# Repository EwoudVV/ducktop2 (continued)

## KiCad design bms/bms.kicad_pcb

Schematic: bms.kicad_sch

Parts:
C724: 470n 25V CP1; effective >=100n at11V; C_0603_1608Metric; MPN GRM188R71E474KA12D
C840: 1u 25V BAT supply; C_0603_1608Metric; MPN GRM188R71E105KA12D
C841: 1u 10V REG18; C_0603_1608Metric; MPN GRM188R71A105KA61D
C845: 4.7u 10V REG1; effective >=1u; C_0805_2012Metric; MPN GRM21BR71A475KA73L
C846: 100n 50V differential current filter; C_0603_1608Metric; MPN GRM188R71H104KA93D
C852, C853, C854, C855: 220n 50V cell filter; C_0603_1608Metric; MPN GRM188R71H224KA93D
C880: 1u 50V REGIN input; C_0805_2012Metric; MPN GRM21BR71H105KA12L
C881: 10u 25V REGIN; effective >=2u; C_0805_2012Metric; MPN GRM21BZ71E106KE15L
C882: 100n 25V C0G startup ramp; C_1206_3216Metric; MPN C1206C104F3GECAUTO
C883: 1u 50V startup input; C_0805_2012Metric; MPN GRM21BR71H105KA12L
C884: 220n 50V startup output; effective >=100n; C_0603_1608Metric; MPN GRM188R71H224KA93D
C2200: 100n 50V thermal regulator input; C_0603_1608Metric; MPN GRM188R71H104KA93D
C2201: 10u 50V thermal bias; require Ceff >=2u; C_1206_3216Metric; MPN CGA5L1X7R1H106K160AC
C2211, C2212, C2213: 10n 50V NTC sense filter; C_0603_1608Metric; MPN GRM188R71H103KA01D
C2221, C2222, C2223: 100n 50V comparator supply; C_0603_1608Metric; MPN GRM188R71H104KA93D
C2230: 100n 50V thermal supervisor supply; C_0603_1608Metric; MPN GRM188R71H104KA93D
C2231: 100n 50V thermal buffer supply; C_0603_1608Metric; MPN GRM188R71H104KA93D
C2232: 100n 50V OFF-bias bypass; C_0603_1608Metric; MPN GRM188R71H104KA93D
C2240, C2241, C2242: 10n 50V thermal reference filter; C_0603_1608Metric; MPN GRM188R71H103KA01D
C2243: 10n 50V thermal reference filter; C_0402_1005Metric; MPN C1005X7R1H103K050BB
C2250, C2251: 100n 50V I2C isolator supply; C_0603_1608Metric; MPN GRM188R71H104KA93D
C2252: 100n 50V bus buffer supply; C_0603_1608Metric; MPN GRM188R71H104KA93D
C2253: 100n 50V readiness buffer supply; C_0603_1608Metric; MPN GRM188R71H104KA93D
C2255, C2256: 100n 50V readiness isolator supply; C_0603_1608Metric; MPN GRM188R71H104KA93D
C2257: 1u 10V control input; C_0603_1608Metric; MPN GRM188R71A105KA61D
C2258: 1u 10V control output; C_0603_1608Metric; MPN GRM188R71A105KA61D
C2270, C2271: 10n 50V C0G differential filter; C_0603_1608Metric; MPN GRM1885C1H103JA01J
C2272: 1u 10V reference input; C_0603_1608Metric; MPN GRM188R71A105KA61D
C2273: 1u 10V reference output; C_0603_1608Metric; MPN GRM188R71A105KA61D
C2274, C2275: 100n 50V current guard supply; C_0603_1608Metric; MPN GRM188R71H104KA93D
C2276, C2277: 10n 50V current reference filter; C_0603_1608Metric; MPN GRM188R71H103KA01D
C2278: 100n 50V current supervisor supply; C_0603_1608Metric; MPN GRM188R71H104KA93D
C2279: 100n 50V readiness logic supply; C_0603_1608Metric; MPN GRM188R71H104KA93D
C2280: 100n 50V reference output; C_0603_1608Metric; MPN GRM188R71H104KA93D
C2281: 1u 50V thermal switch input; C_0805_2012Metric; MPN GRM21BR71H105KA12L
D840: BAT54WS BAT supply reverse block; D_SOD-323; MPN BAT54WS-7-F
D847, D848: BZT52C15 gate-source clamp; D_SOD-123; MPN BZT52C15-7-F
D849: BZT52C5V1 startup permit VGS clamp; D_SOD-123; MPN BZT52C5V1-7-F
D2220, D2221: BAT54WS OFF-bias supply OR; D_SOD-323; MPN BAT54WS-7-F
F1: 10A fast pack fuse; Schurter_HCF_8.05x5mm; MPN 3-101-051
J2: raw pack power: 1 negative, 2 positive; WAGO_2060_452_SMD; MPN 2060-452/998-404
J2072: protected pack power; WAGO_2060_452_SMD; MPN 2060-452/998-404
J2074: isolated bms control; JST_SH_SM05B-SRSS-TB_1x05-1MP_P1.00mm_Horizontal; MPN SM05B-SRSS-TB(LF)(SN)
J2200: three cell probes: paired 1/2, 3/4, 5/6; JST_SH_SM06B-SRSS-TB_1x06-1MP_P1.00mm_Horizontal; MPN SM06B-SRSS-TB(LF)(SN)
J2201: cell taps: 1 cell 1, 2 cell 2; JST_GH_SM02B-GHS-TB_1x02-1MP_P1.25mm_Horizontal; MPN SM02B-GHS-TB(LF)(SN)
Q11: CSD18540Q5B high-side charge; CSD18540Q5B_DNK; MPN CSD18540Q5B
Q12: CSD18540Q5B high-side discharge; CSD18540Q5B_DNK; MPN CSD18540Q5B
Q2200: BSS138 CHG thermal CTR pull-down; SOT-23; MPN BSS138LT1G
Q2201: BSS138 DSG thermal CTR pull-down; SOT-23; MPN BSS138LT1G
Q2211: ZXMP6A13FTA PDSG signal translator; SOT-23; MPN ZXMP6A13FTA
Q2212: BSS138 independent discharge inhibit; SOT-23; MPN BSS138LT1G
R840: 100R BAT input filter; R_0603_1608Metric; MPN RC0603FR-07100RL
R841, R842, R843, R844: 75R 1% cell input/balance filter; R_0603_1608Metric; MPN RC0603FR-0775RL
R845: 100R SRP filter; R_0603_1608Metric; MPN RC0603FR-07100RL
R846: 100R SRN filter; R_0603_1608Metric; MPN RC0603FR-07100RL
R847, R848: 100R gate series; R_0603_1608Metric; MPN RC0603FR-07100RL
R849, R850: 1M gate-source; R_0603_1608Metric; MPN RC0603FR-071ML
R851: 10k PACK sense; R_0603_1608Metric; MPN RC0603FR-0710KL
R852: 10k LD sense; R_0603_1608Metric; MPN RC0603FR-0710KL
R870, R871: DNP 0R drive release; R_0603_1608Metric; MPN RC0603JR-070RL; not fitted
R872: DNP 0R startup drive release; R_0603_1608Metric; MPN RC0603JR-070RL; not fitted
R880, R881: 430R 1% 1.5W REGIN supply limiter; R_2512_6332Metric; MPN CRCW2512430RFKEGHP
R882: 100k reset default-low; R_0603_1608Metric; MPN RC0603FR-07100KL
R883: 10k TS1 termination; R_0603_1608Metric; MPN RC0603FR-0710KL
R884: 100k UVLO top; R_0603_1608Metric; MPN RC0603FR-07100KL
R885: 24.9k UVLO bottom; R_0603_1608Metric; MPN RC0603FR-0724K9L
R886: 402k latched current-limit mode; R_0603_1608Metric; MPN RC0603FR-07402KL
R887: 12k 0.1% 25ppm ILIM; R_0603_1608Metric; MPN TNPW060312K0BEEN
R888: 24k 0.1% 25ppm ILIM; R_0603_1608Metric; MPN TNPW060324K0BEEN
R889: 100k startup fault pull-up; R_0603_1608Metric; MPN RC0603FR-07100KL
R890: 1k PDSG translator gate; R_0603_1608Metric; MPN RC0603FR-071KL
R891: 1M translator gate-source; R_0603_1608Metric; MPN RC0603FR-071ML
R892: 100k startup shutdown top; R_0603_1608Metric; MPN RC0603FR-07100KL
R893: 33.2k startup shutdown default-low; R_0603_1608Metric; MPN RC0603FR-0733K2L
R894: 100k startup permit gate series; R_0603_1608Metric; MPN RC0603FR-07100KL
R2200: 1k 1% 0.75W raw thermal supply limiter; R_2010_5025Metric; MPN RC2010FK-071KL
R2201: 9.53k 0.1% 25ppm thermal bias fault bleed; R_0603_1608Metric; MPN RT0603BRD079K53L
R2210, R2213, R2216: 100k 0.1% 25ppm cell NTC pull-up; R_0603_1608Metric; MPN RT0603BRD07100KL
R2211, R2214: 10k 0.1% 25ppm NTC sense-lead limit; R_0603_1608Metric; MPN RT0603BRD0710KL
R2212, R2215, R2218: 10k 0.1% 25ppm NTC return-lead limit; R_0603_1608Metric; MPN RT0603BRD0710KL
R2217: 10k 0.1% 25ppm NTC sense-lead limit; R_0402_1005Metric; MPN RT0402BRD0710KL
R2230: 100k thermal charge-health pull-up; R_0603_1608Metric; MPN RC0603FR-07100KL
R2231: 100k thermal discharge-health pull-up; R_0603_1608Metric; MPN RC0603FR-07100KL
R2232: 47k thermal-ready pull-up; R_0603_1608Metric; MPN RC0603FR-0747KL
R2233: 1M thermal-ready default-low; R_0603_1608Metric; MPN RC0603FR-071ML
R2234, R2237: 1k thermal CTR gate series; R_0603_1608Metric; MPN RC0603FR-071KL
R2235, R2238: 100k thermal CTR gate default-off; R_0603_1608Metric; MPN RC0603FR-07100KL
R2236, R2239: 10k hardware OFF default-high; R_0603_1608Metric; MPN RC0603FR-0710KL
R2240: 243k 0.1% 25ppm CHG_COLD top; R_0603_1608Metric; MPN RT0603BRD07243KL
R2241, R2243, R2245, R2247: 499k 0.1% 25ppm thermal reference bottom; R_0603_1608Metric; MPN RT0603BRD07499KL
R2242: 634k 0.1% 25ppm CHG_HOT top; R_0603_1608Metric; MPN RT0603BRD07634KL
R2244: 147k 0.1% 25ppm DSG_COLD top; R_0603_1608Metric; MPN RT0603BRD07147KL
R2246: 845k 0.1% 25ppm DSG_HOT top; R_0603_1608Metric; MPN RT0603BRD07845KL
R2251: 100k raw health default-low; R_0603_1608Metric; MPN RC0603FR-07100KL
R2255: 100k control health default-low; R_0603_1608Metric; MPN RC0603FR-07100KL
R2258: 4.7k readiness output current limit; R_0603_1608Metric; MPN RC0603FR-074K7L
R2260, R2261: 4.7k 1% I2C pull-up; R_0603_1608Metric; MPN RC0603FR-074K7L
R2262, R2263, R2266, R2267: 2.2k 1% I2C pull-up; R_0603_1608Metric; MPN RC0603FR-072K2L
R2270: 10.2k 0.1% 25ppm current limit; R_0603_1608Metric; MPN TNPW060310K2BEEA
R2271: 26.7k 0.1% 25ppm current limit; R_0603_1608Metric; MPN TNPW060326K7BEEA
R2272: 16.9k 0.1% 25ppm current limit; R_0603_1608Metric; MPN TNPW060316K9BEEA
R2273: 31.6k 0.1% 25ppm current limit; R_0603_1608Metric; MPN TNPW060331K6BEEA
R2274: 10k current-ready pull-up; R_0603_1608Metric; MPN RC0603FR-0710KL
R2275: 100k current-ready default-low; R_0603_1608Metric; MPN RC0603FR-07100KL
R2276: 100k current reset pull-up; R_0603_1608Metric; MPN RC0603FR-07100KL
R2277: 100k 180..420ms current hold; R_0603_1608Metric; MPN RC0603FR-07100KL
R2278: 100k permission default-low; R_0603_1608Metric; MPN RC0603FR-07100KL
R2280, R2281, R2282, R2283: 4.99R 0.1% 25ppm sense filter; R_0603_1608Metric; MPN TNPW06034R99BEEA
R2290: 390k thermal switch default-off; R_0603_1608Metric; MPN RC0603FR-07390KL
RS11: 2mOhm 1% 6W four-terminal pack shunt; Bourns_CSS4J_4026_Kelvin; MPN CSS4J-4026K-2L00F
TH2201: 104JT-025 cell 1 insulated probe; MPN 104JT-025
TH2202: 104JT-025 cell 2 insulated probe; MPN 104JT-025
TH2203: 104JT-025 cell 3 insulated probe; MPN 104JT-025
TPB1: PACK_POS_RAW; TestPoint_Pad_D1.0mm
TPB2: BAT_PROT_VIN; TestPoint_Pad_D1.0mm
TPB3: PACK_POS_FUSED; TestPoint_Pad_D1.0mm
TPB4: BAT_PROT_FET_COMMON; TestPoint_Pad_D1.0mm
TPB5: PACK_NEG_RAW; TestPoint_Pad_D1.0mm
TPB6: FG_VSS; TestPoint_Pad_D1.0mm
TPB7: BQ_BAT; TestPoint_Pad_D1.0mm
TPB8: BQ_WAKE; TestPoint_Pad_D1.0mm
TPB9: BQ_RST_SHUT; TestPoint_Pad_D1.0mm
TPB10: BQ_REG1; TestPoint_Pad_D1.0mm
TPB11: BMS_SRP; TestPoint_Pad_D1.0mm
TPB12: BMS_SRN; TestPoint_Pad_D1.0mm
TPB13: BMS_RAW_SCL; TestPoint_Pad_D1.0mm
TPB14: BMS_RAW_SDA; TestPoint_Pad_D1.0mm
TPB15: BQ_ALERT_AWAKE; TestPoint_Pad_D1.0mm
TPB16: BQ_REGIN; TestPoint_Pad_D1.0mm
TPB20: THERM_3V3; TestPoint_Pad_D1.0mm
TPB21: THERM_READY; TestPoint_Pad_D1.0mm
TPB22: THERM_SENSE_1; TestPoint_Pad_D1.0mm
TPB23: THERM_SENSE_2; TestPoint_Pad_D1.0mm
TPB24: THERM_SENSE_3; TestPoint_Pad_D1.0mm
TPB25: BMS_CFETOFF; TestPoint_Pad_D1.0mm
TPB26: BMS_DFETOFF; TestPoint_Pad_D1.0mm
TPB27: BMS_PERMIT_READY; TestPoint_Pad_D1.0mm
TPB30: PDSG_FLT_N; TestPoint_Pad_D1.0mm
TPB31: PDSG_SHDN; TestPoint_Pad_D1.0mm
TPB32: PDSG_RTN; TestPoint_Pad_D1.0mm
TPB33: CURRENT_READY; TestPoint_Pad_D1.0mm
TPB34: CURRENT_CLR_N; TestPoint_Pad_D1.0mm
TPB35: BMS_CURRENT_REF; TestPoint_Pad_D1.0mm
U708: TPS70950DBVR REGIN supply; SOT-23-5; MPN TPS70950DBVR
U719: BQ76922RSNR three-cell monitor and protector; TI_RSN0032B_WQFN32_4x4mm; MPN BQ76922RSNR
U2200: TPS70933DBVR raw-pack thermal bias; SOT-23-5; MPN TPS70933DBVR
U2201: TLV1864PWR cell 1 thermal windows; TSSOP-14_4.4x5mm_P0.65mm; MPN TLV1864PWR
U2202: TLV1864PWR cell 2 thermal windows; TSSOP-14_4.4x5mm_P0.65mm; MPN TLV1864PWR
U2203: TLV1864PWR cell 3 thermal windows; TSSOP-14_4.4x5mm_P0.65mm; MPN TLV1864PWR
U2204: TLV803EA29RDBZR thermal startup hold; SOT-23; MPN TLV803EA29RDBZR
U2205: SN74AUP2G126DCUR thermal startup gate; TI_DCU0008A_VSSOP8; MPN SN74AUP2G126DCUR
U2206: ISO1640BDR BQ I2C isolation; SOIC-8_3.9x4.9mm_P1.27mm; MPN ISO1640BDR
U2207: TCA9517AIDGKR isolated-bus buffer; VSSOP-8_3x3mm_P0.65mm; MPN TCA9517AIDGKR
U2208: SN74LVC1G17DBVR raw readiness buffer; SOT-23-5; MPN SN74LVC1G17DBVR
U2209: ISO7021FDR readiness isolation; default low; SOIC-8_3.9x4.9mm_P1.27mm; MPN ISO7021FDR
U2210: INA381A3IDGSR discharge current latch; MSOP-10_3x3mm_P0.5mm; MPN INA381A3IDGSR
U2211: INA381A4IDGSR charge current latch; MSOP-10_3x3mm_P0.5mm; MPN INA381A4IDGSR
U2213: REF3425IDBVR current-trip reference; SOT-23-6; MPN REF3425IDBVR
U2214: TPS3808G30DBVR current startup hold; SOT-23-6; MPN TPS3808G30DBVR
U2215: SN74LVC1G08DBVR temperature/current readiness; SOT-23-5; MPN SN74LVC1G08DBVR
U2216: TPS22941DCKR control supply current limit; SOT-353_SC-70-5; MPN TPS22941DCKR
U2217: TPS22810DBVR thermal supply shutdown; SOT-23-6; MPN TPS22810DBVR
U2218: TPS26600PWPR latched startup current limit; HTSSOP16_EP_ThermalVias; MPN TPS26600PWPR

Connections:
/BAT_PROT_FET_COMMON: Q11.5 (D(5-8)), Q12.5 (D(5-8)), TPB4.1
/BAT_PROT_VIN: C883.1, D847.2 (A), F1.2, Q11.1 (S), Q11.2 (S), Q11.3 (S), R849.2, R884.1, TPB2.1, U2218.1 (IN), U2218.2 (IN)
/BMS_CFETOFF: Q2200.3 (D), R2236.2, TPB25.1, U719.19 (CFETOFF)
/BMS_CURRENT_REF: C2273.1, C2280.1, R2270.1, R2272.1, TPB35.1, U2213.5 (OUT_S), U2213.6 (OUT_F)
/BMS_DFETOFF: Q2201.3 (D), R2239.2, TPB26.1, U719.20 (DFETOFF)
/BMS_FG_KELVIN: R846.1, R2280.1, R2283.1, RS11.4 (SENSE_FET)
/BMS_MONITOR_READY_RAW: R2251.1, U2208.4, U2209.3 (INB)
/BMS_OC_CHG_IN_N: C2271.2, R2283.2, U2211.10 (IN-)
/BMS_OC_CHG_IN_P: C2271.1, R2282.2, U2211.1 (IN+)
/BMS_OC_CHG_LIMIT: C2277.1, R2272.2, R2273.1, U2211.7 (CMPREF)
/BMS_OC_CHG_OUT: U2211.8 (CMPIN), U2211.9 (VOUT)
/BMS_OC_DSG_IN_N: C2270.2, R2281.2, U2210.10 (IN-)
/BMS_OC_DSG_IN_P: C2270.1, R2280.2, U2210.1 (IN+)
/BMS_OC_DSG_LIMIT: C2276.1, R2270.2, R2271.1, U2210.7 (CMPREF)
/BMS_OC_DSG_OUT: U2210.8 (CMPIN), U2210.9 (VOUT)
/BMS_OFF_BIAS: C2232.1, D2220.1 (K), D2221.1 (K), R2236.1, R2239.1
/BMS_PERMIT_READY: R2278.1, TPB27.1, U2205.1 (1OE), U2205.7 (2OE), U2215.4
/BMS_RAW_KELVIN: R845.1, R2281.1, R2282.1, RS11.3 (SENSE_RAW)
/BMS_RAW_SCL: R2260.2, TPB13.1, U719.17 (SCL), U2206.6 (SCL2)
/BMS_RAW_SDA: R2261.2, TPB14.1, U719.18 (SDA), U2206.7 (SDA2)
/BMS_SRN: C846.2, R846.2, TPB12.1, U719.12 (SRN)
/BMS_SRP: C846.1, R845.2, TPB11.1, U719.11 (SRP)
/BQ_ALERT_AWAKE: R2290.1, TPB15.1, U719.16 (ALERT), U2217.3 (EN_UVLO)
/BQ_BAT: C724.2, C840.1, Q2211.2 (S), R840.2, R891.2, TPB7.1, U719.1 (BAT)
/BQ_BAT_FEED: D840.1 (K), R840.1
/BQ_CHG: R870.1, U719.31 (CHG)
/BQ_CP1: C724.1, U719.32 (CP1)
/BQ_DSG: R871.1, U719.30 (DSG)
/BQ_LD: R852.2, U719.28 (LD)
/BQ_PACK: R851.2, U719.29 (PACK)
/BQ_PDSG: R890.1, U719.26 (PDSG)
/BQ_REG1: C845.1, C2250.1, C2253.1, C2255.1, C2272.1, C2274.1, C2275.1, C2278.1, D2221.2 (A), R889.1, R2260.1, R2261.1, R2274.1, R2276.1, R2277.1, TPB10.1, U719.22 (REG1), U2206.8 (VCC2), U2208.5 (VCC), U2209.1 (VCC1), U2210.2 (VS), U2211.2 (VS), U2213.3 (EN), U2213.4 (IN), U2214.5 (SENSE), U2214.6 (VDD)
/BQ_REG18: C841.1, U719.15 (REG18)
/BQ_REGIN: C881.1, TPB16.1, U708.5 (OUT), U719.23 (REGIN), U719.24 (BREG)
/BQ_REGIN_FEED: C880.1, R880.2, R881.2, U708.1 (IN)
/BQ_RST_SHUT: R882.1, TPB9.1, U719.21 (RST_SHUT)
/BQ_TS1: R883.1, U719.13 (TS1)
/BQ_VC0: C852.1, C853.2, R841.2, U719.9 (VC0)
/BQ_VC1: C853.1, C854.2, R842.2, U719.8 (VC1)
/BQ_VC2: C854.1, C855.2, R843.2, U719.3 (VC4A), U719.4 (VC4B), U719.5 (VC3A), U719.6 (VC3B), U719.7 (VC2)
/BQ_VC5: C855.1, R844.2, U719.2 (VC5)
/BQ_WAKE: TPB8.1, U719.14 (TS2)
/CELL1_TAP: J2201.1, R842.1
/CELL2_TAP: J2201.2, R843.1
/CHG_DRV_RELEASED: R847.1, R870.2
/CHG_GATE: D847.1 (K), Q11.4 (G), R847.2, R849.1
/CTRL_3V3: C2251.1, C2252.1, C2256.1, C2258.1, R2262.1, R2263.1, R2266.1, R2267.1, U2206.1 (VCC1), U2207.1 (VCCA), U2207.5 (EN), U2207.8 (VCCB), U2209.8 (VCC2), U2216.1 (VOUT)
/CTRL_GND: C2251.2, C2252.2, C2256.2, C2257.2, C2258.2, J2074.5, J2074.MP (MountPin), R2255.2, U2206.4 (GND1), U2207.4 (GND), U2209.5 (GND2), U2209.7 (INA), U2216.2 (GND), U2216.4 (ON_N)
/CTRL_MONITOR_READY: R2258.1, U2209.6 (OUTB)
/CURRENT_CLR_N: R2276.2, TPB34.1, U2214.3 (MR_N)
/CURRENT_DELAY: R2277.2, U2214.4 (CT)
/CURRENT_READY: R2274.2, R2275.1, TPB33.1, U2210.4 (RESET), U2211.4 (RESET), U2214.1 (RESET_N), U2215.2
/DSG_DRV_RELEASED: R848.1, R871.2
/DSG_GATE: D848.1 (K), Q12.4 (G), R848.2, R850.1
/FG_VSS: C884.2, J2072.2, RS11.2 (FORCE_FET), TPB6.1
/ISO_CTRL_SCL: R2262.2, U2206.3 (SCL1), U2207.2 (SCLA)
/ISO_CTRL_SDA: R2263.2, U2206.2 (SDA1), U2207.3 (SDAA)
/MCU_3V3: C2257.1, J2074.3, U2216.5 (VIN)
/PACK_I2C_SCL: J2074.2, R2266.2, U2207.7 (SCLB)
/PACK_I2C_SDA: J2074.4, R2267.2, U2207.6 (SDAB)
/PACK_MONITOR_READY: J2074.1, R2255.1, R2258.2, U2216.3 (OC_N)
/PACK_NEG_RAW: C840.2, C841.2, C845.2, C852.2, C880.2, C881.2, C883.2, C2200.2, C2201.2, C2211.2, C2212.2, C2213.2, C2221.2, C2222.2, C2223.2, C2230.2, C2231.2, C2232.2, C2240.2, C2241.2, C2242.2, C2243.2, C2250.2, C2253.2, C2255.2, C2272.2, C2273.2, C2274.2, C2275.2, C2276.2, C2277.2, C2278.2, C2279.2, C2280.2, C2281.2, J2.1, J2200.MP, J2201.MP, Q2200.2 (S), Q2201.2 (S), R841.1, R882.2, R883.2, R2201.2, R2212.2, R2215.2, R2218.2, R2233.2, R2235.2, R2238.2, R2241.2, R2243.2, R2245.2, R2247.2, R2251.2, R2271.2, R2273.2, R2275.2, R2278.2, R2290.2, RS11.1 (FORCE_RAW), TPB5.1, U708.2 (GND), U719.10 (VSS), U719.33 (EP), U2200.2 (GND), U2201.11 (V-), U2202.11 (V-), U2203.11 (V-), U2204.2 (GND), U2205.4 (GND), U2206.5 (GND2), U2208.3 (GND), U2209.4 (GND1), U2210.5 (GND), U2211.5 (GND), U2213.1 (GND_F), U2213.2 (GND_S), U2214.2 (GND), U2215.3 (GND), U2217.2 (GND), U2218.9 (GND)
/PACK_POS_FUSED: C884.1, D848.2 (A), J2072.1, Q12.1 (S), Q12.2 (S), Q12.3 (S), R850.2, R851.1, R852.1, TPB3.1, U2218.15 (OUT), U2218.16 (OUT)
/PACK_POS_RAW: D840.2 (A), F1.1, J2.2, R844.1, R880.1, R881.1, R2200.1, TPB1.1
/PDSG_CTRL_GATE: Q2211.1 (G), R890.2, R891.1
/PDSG_CTRL_HIGH: Q2211.3 (D), R872.1
/PDSG_CTRL_RELEASED: R872.2, R892.1
/PDSG_DVDT: C882.1, U2218.12 (DV_DT)
/PDSG_FLT_N: R889.2, TPB30.1, U2218.14 (FLT_N)
/PDSG_ILIM: R887.1, R888.1, U2218.11 (ILIM)
/PDSG_MODE: R886.1, U2218.6 (MODE)
/PDSG_PERMIT_GATE: D849.1 (K), Q2212.1 (G), R894.2
/PDSG_RTN: C882.2, R885.2, R886.2, R887.2, R888.2, R893.2, TPB32.1, U2218.5 (OVP), U2218.8 (RTN), U2218.17 (EP_RTN)
/PDSG_SHDN: D849.2 (A), Q2212.2 (S), R893.1, TPB31.1, U2218.7 (SHDN)
/PDSG_SHDN_DRIVE: Q2212.3 (D), R892.2
/PDSG_UVLO: R884.2, R885.1, U2218.3 (UVLO)
/THERM_3V3: C2201.1, C2221.1, C2222.1, C2223.1, C2230.1, C2231.1, C2279.1, D2220.2 (A), R2201.1, R2210.1, R2213.1, R2216.1, R2230.1, R2231.1, R2232.1, R2240.1, R2242.1, R2244.1, R2246.1, TPB20.1, U2200.5 (OUT), U2201.4 (V+), U2202.4 (V+), U2203.4 (V+), U2204.3 (VDD), U2205.8 (VCC), U2215.5 (VCC)
/THERM_CHG_COLD_REF: C2240.1, R2240.2, R2241.1, U2201.3 (IN1+), U2202.3 (IN1+), U2203.3 (IN1+)
/THERM_CHG_GATE: Q2200.1 (G), R2234.2, R2235.1
/THERM_CHG_HEALTH: R2230.2, U2201.1 (OUT1), U2201.7 (OUT2), U2202.1 (OUT1), U2202.7 (OUT2), U2203.1 (OUT1), U2203.7 (OUT2), U2205.2 (1A), U2211.3 (ALERT_N)
/THERM_CHG_HOT_REF: C2241.1, R2242.2, R2243.1, U2201.6 (IN2-), U2202.6 (IN2-), U2203.6 (IN2-)
/THERM_CHG_PERMIT: R2234.1, U2205.6 (1Y)
/THERM_DSG_COLD_REF: C2242.1, R2244.2, R2245.1, U2201.12 (IN4+), U2202.12 (IN4+), U2203.12 (IN4+)
/THERM_DSG_GATE: Q2201.1 (G), R894.1, R2237.2, R2238.1
/THERM_DSG_HEALTH: R2231.2, U2201.8 (OUT3), U2201.14 (OUT4), U2202.8 (OUT3), U2202.14 (OUT4), U2203.8 (OUT3), U2203.14 (OUT4), U2205.5 (2A), U2210.3 (ALERT_N)
/THERM_DSG_HOT_REF: C2243.1, R2246.2, R2247.1, U2201.9 (IN3-), U2202.9 (IN3-), U2203.9 (IN3-)
/THERM_DSG_PERMIT: R2237.1, U2205.3 (2Y)
/THERM_PROBE_1_A: J2200.1, R2211.2, TH2201.1
/THERM_PROBE_1_B: J2200.2, R2212.1, TH2201.2
/THERM_PROBE_2_A: J2200.3, R2214.2, TH2202.1
/THERM_PROBE_2_B: J2200.4, R2215.1, TH2202.2
/THERM_PROBE_3_A: J2200.5, R2217.2, TH2203.1
/THERM_PROBE_3_B: J2200.6, R2218.1, TH2203.2
/THERM_RAW_IN: C2200.1, U2200.1 (IN), U2217.5 (QOD), U2217.6 (VOUT)
/THERM_RAW_PRE: C2281.1, R2200.2, U2217.1 (VIN)
/THERM_READY: R2232.2, R2233.1, TPB21.1, U2204.1 (RESETz), U2208.2, U2215.1
/THERM_SENSE_1: C2211.1, R2210.2, R2211.1, TPB22.1, U2201.2 (IN1-), U2201.5 (IN2+), U2201.10 (IN3+), U2201.13 (IN4-)
/THERM_SENSE_2: C2212.1, R2213.2, R2214.1, TPB23.1, U2202.2 (IN1-), U2202.5 (IN2+), U2202.10 (IN3+), U2202.13 (IN4-)
/THERM_SENSE_3: C2213.1, R2216.2, R2217.1, TPB24.1, U2203.2 (IN1-), U2203.5 (IN2+), U2203.10 (IN3+), U2203.13 (IN4-)

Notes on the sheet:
== three-cell BMS: high-side protection, cell monitoring and independent inhibits ==
8 A discharge / 3 A charge design targets; installed current, startup and temperature limits need bench verification.
Leave the three drive-release links open until configuration and fault tests pass.
CTRL_GND stays isolated from RAW and FG. All external pack current crosses RS11 and the center gauge shunt.
Raw service pads: use an isolated programmer. Do not attach system-ground equipment across either shunt.
== three-cell temperature inhibit: raw reference, independent of firmware ==
J2200 and its hold-downs are raw-pack referenced; no system-ground wire.
Charge10..40C / discharge0..50C design windows. Cell limits and installed probe response need tests.
Loss of either READY signal removes permission. The hardware inhibit covers main FETs and the startup branch.
== current guards: signed low-side sense, hardware latches ==
Nominal trips: about9.1A discharge and4.1A charge. These are fault trips, not operating ratings.
CLR is a raw-side service input. The five-wire control harness does not reset these latches.
== startup branch: active current limit, thermal latch-off ==
PDSG timeout stays0; only voltage completion may enable the main DSG path.
PDSG_RTN is the local eFuse reference. Do not bond it to RAW, FG, CTRL or a mounting hole.
The independent discharge permit also covers PDSG; a disabled main FET cannot leave an unchecked bypass.
== isolated control interface: I2C and monitor readiness ==
BQ uses isolator side2. Side1 is a short local bus; the buffer carries the longer harness load.
High readiness means REG1 and the thermal supervisor are powered. Faults and freshness come from verified I2C samples.
The control connector supplies only CTRL_GND. Programming and current-clear pads belong to RAW.

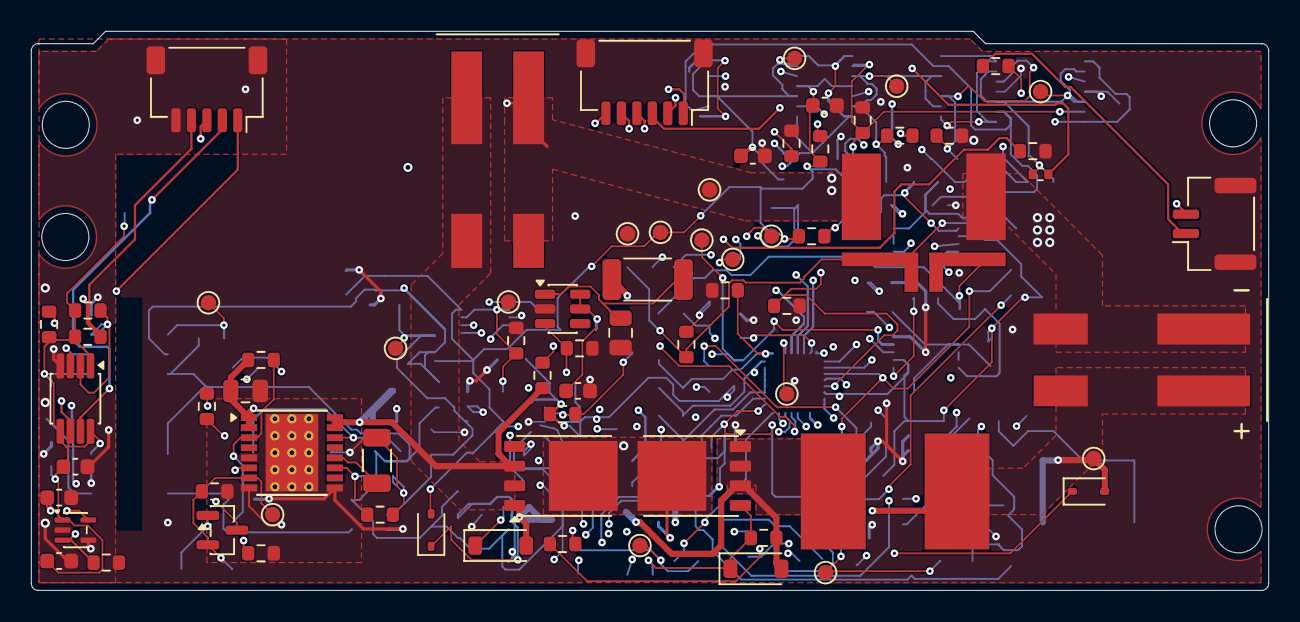
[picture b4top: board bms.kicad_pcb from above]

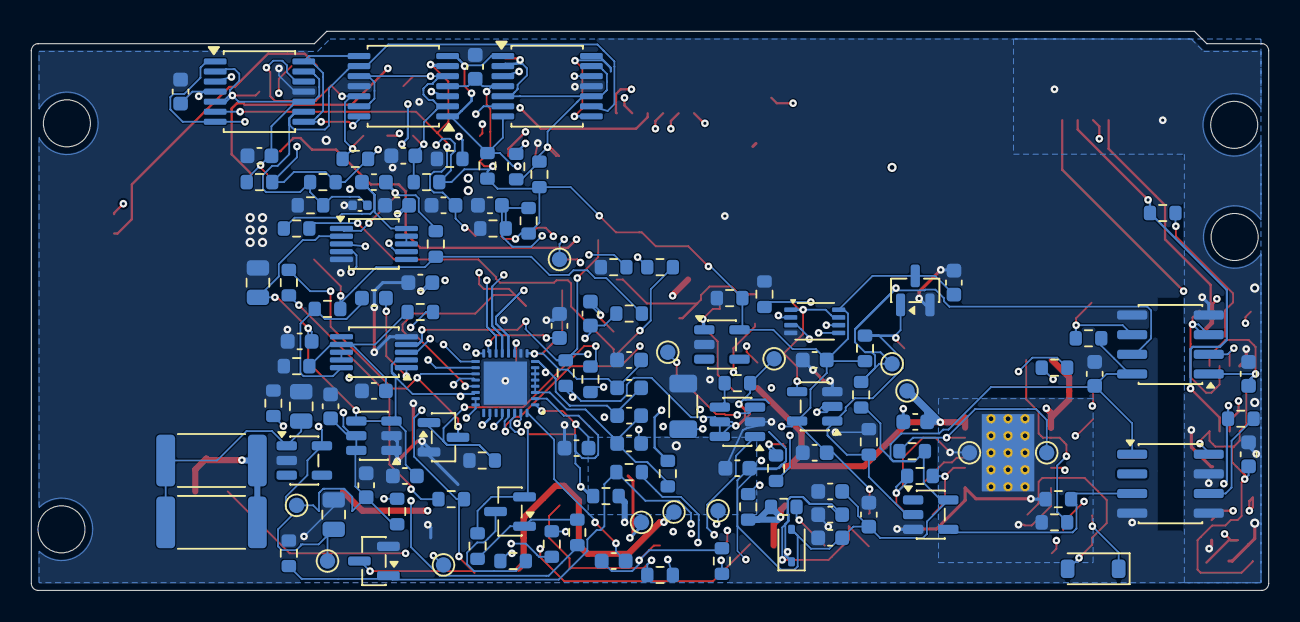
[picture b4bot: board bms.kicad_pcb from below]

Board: 4 copper layers, 80.0 x 36.1 mm, 201 parts (129 on the bottom side), 99 nets.

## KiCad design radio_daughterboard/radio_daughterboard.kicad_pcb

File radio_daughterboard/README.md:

# radio daughterboard

9 october 2026: this is now planned as an external plug-in accessory so the
laptop can have a thinner, flush clamshell case. the radio, GNSS receiver
and separate radio audio codec stay together. the saved electronics still
use the internal 30-pin interface below; converting power, audio and
controls to an external cable is a separate design change. no external
connector or cable is released yet.

the radio/GNSS/audio board is removable. i want the rest of the laptop to
work while it is absent or being revised, including normal system audio,
the microphone, charging, and boot.

it contains DRA818V and DRA818U radio modules, external filters and RF
switches, a MAX-M10S GNSS receiver, and a separate PCM2900C USB audio codec.
power, USB, UART/control, PTT, presence, and fault signals go through the
removable interface. the radio is intended to start off and stay separate
from core laptop power decisions.

## layout state

the 4 september board read found 126 footprints on a four-layer placement
board, with no tracks or vias. the nominal outline is about 120 x 70 mm.

the stored renders show a placement-stage design. they do not prove the
current chassis fit. the center-side FFC connector J2300 is now at (188,4),
rotation 0, so the installed cable route and board supports need a new check.
[mechanical plan](../docs/hardware/mechanical.md)

## source and checks

the schematic hierarchy and placement generator live in `gen/`:

- `generate_radio_daughterboard_project.py`
- `generate_radio_daughterboard_pcb.py`
- `verify_radio_daughterboard.py`

generation can replace source/placement files. use a copied candidate for
a deliberate change, following [the rebuild guidance](../docs/build-and-verify.md#deliberate-rebuilds).
direct ERC and DRC can inspect the existing files without regeneration.

## remaining work

finish placement/routing, test access, the cable installation, and mechanical
supports. then verify rails, default-off behavior, removal/fault handling,
GNSS, control and audio paths. RF filters, antennas, transmit behavior,
emissions, and coexistence need their own measured test setup.

the radio can be deferred during initial laptop bring-up. its removal must
not silently break a shared bus, reset, power, or audio dependency.

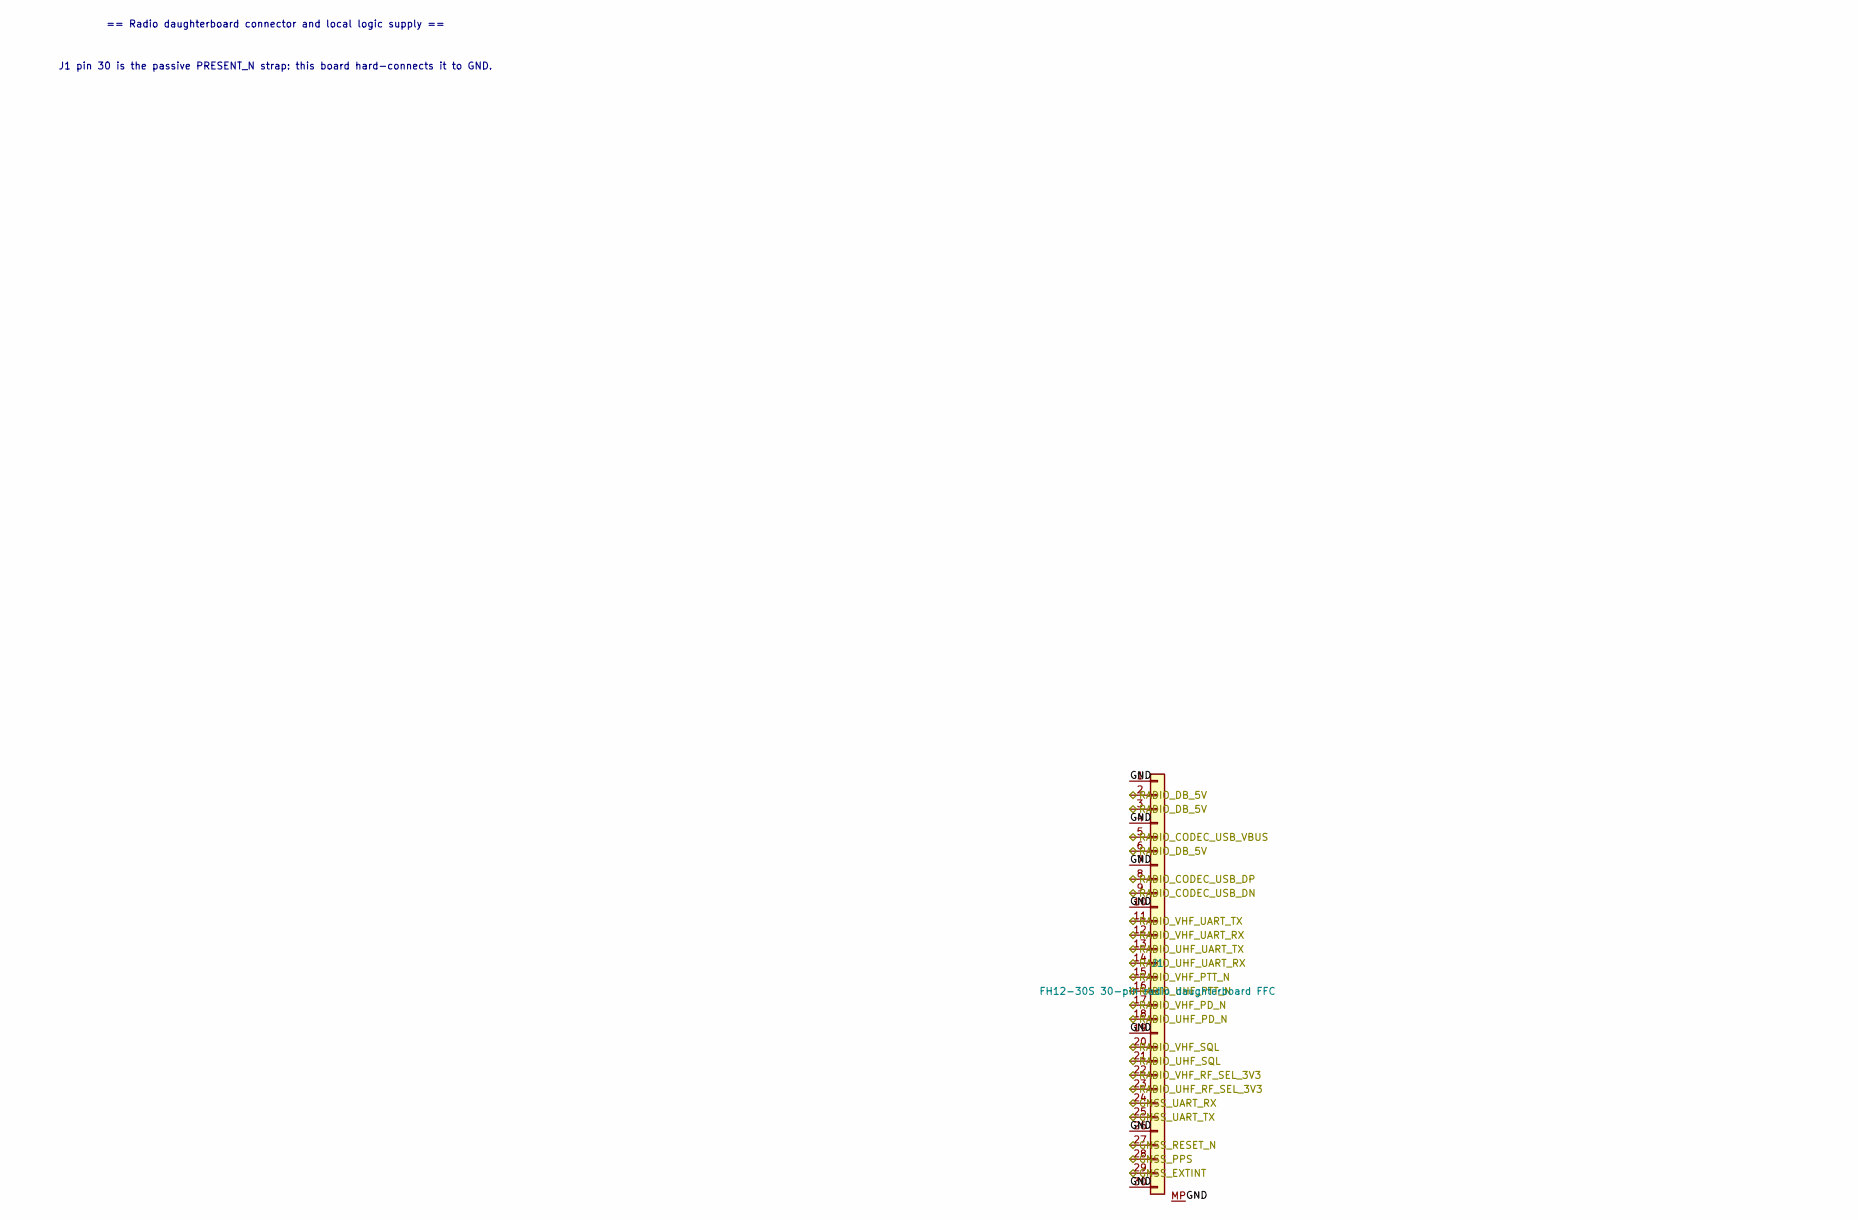
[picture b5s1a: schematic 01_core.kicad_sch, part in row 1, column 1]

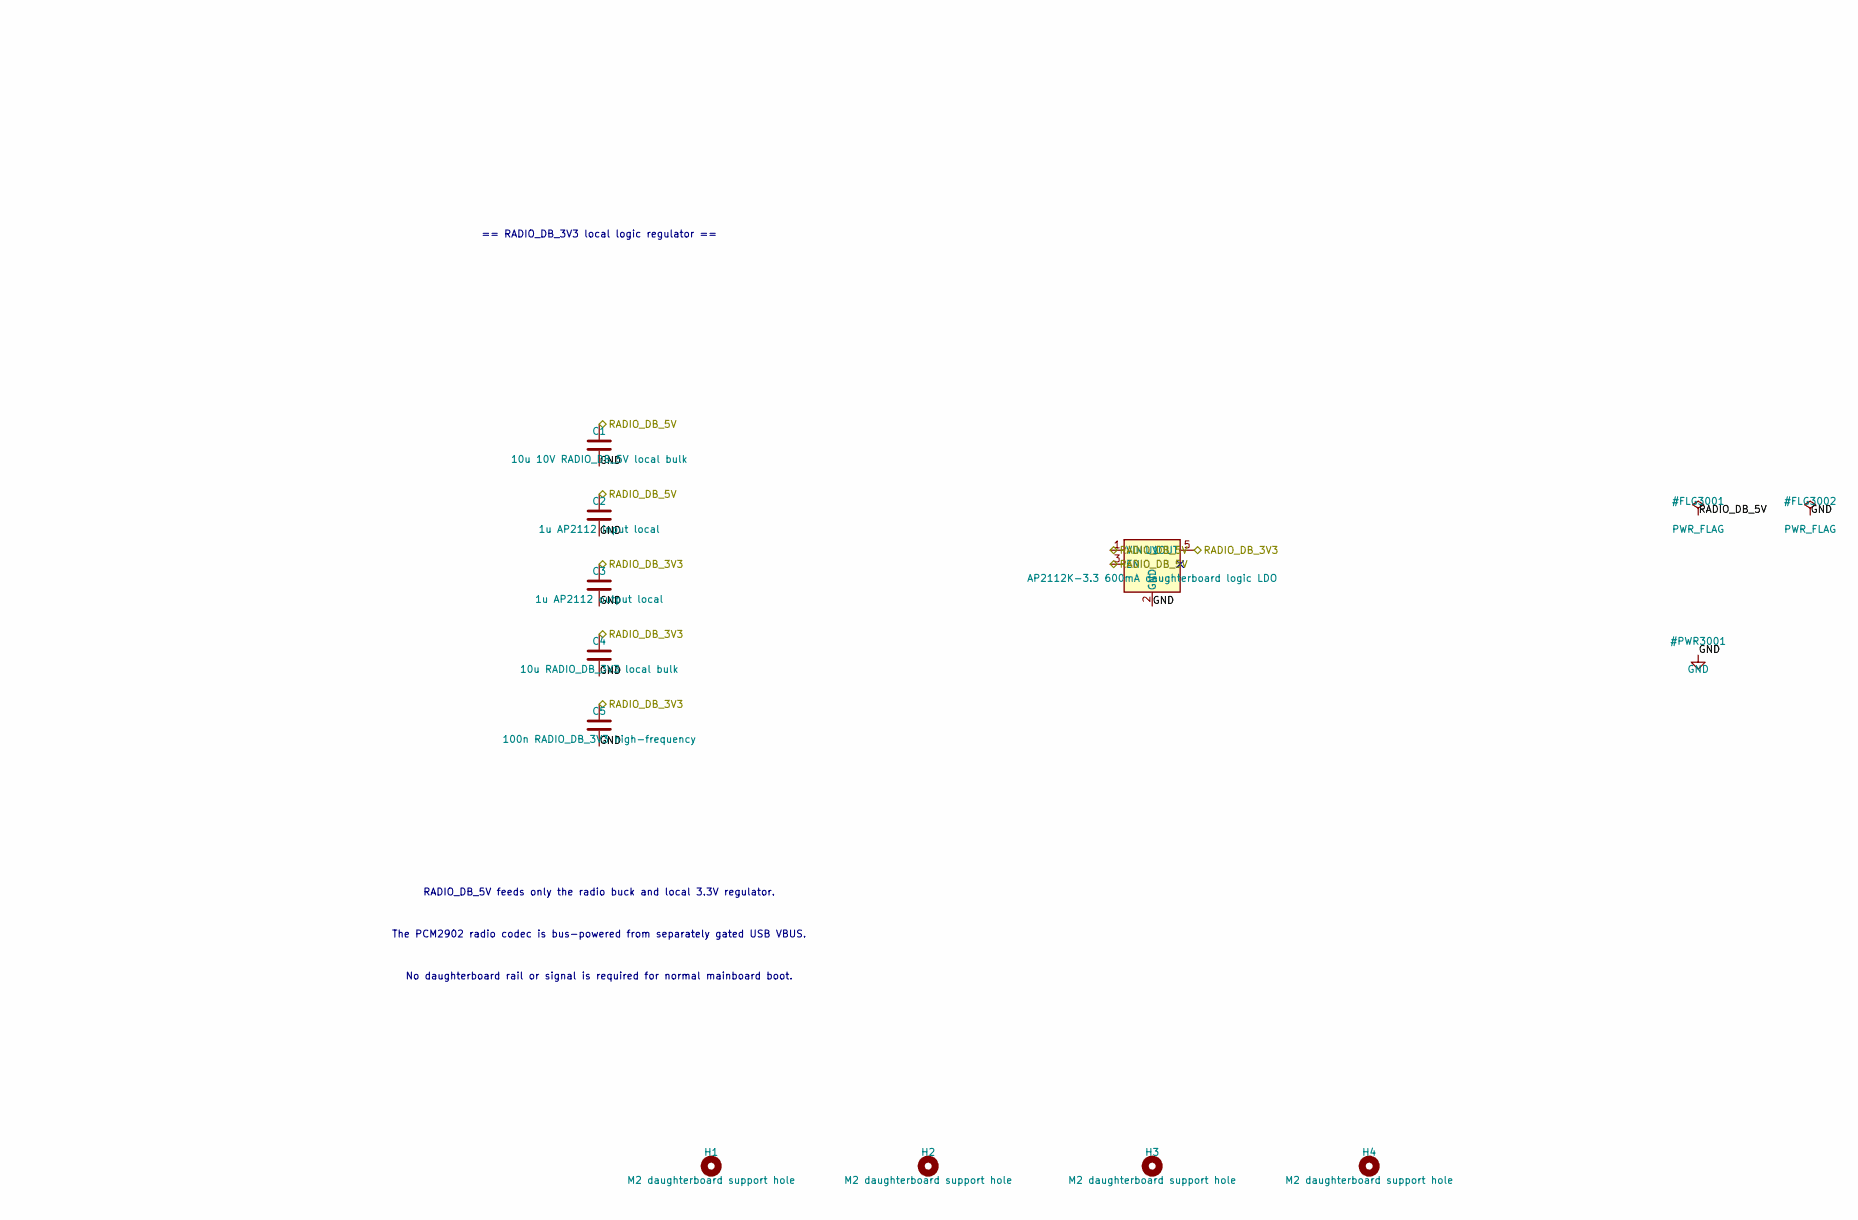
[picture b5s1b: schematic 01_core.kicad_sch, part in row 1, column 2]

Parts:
C1: 10u 10V RADIO_DB_5V local bulk; C_1206_3216Metric; MPN GRM31CR71E106KA12L
C2: 1u AP2112 input local; C_0805_2012Metric; MPN GRM21BR71A105KA01L
C3: 1u AP2112 output local; C_0805_2012Metric; MPN GRM21BR71A105KA01L
C4: 10u RADIO_DB_3V3 local bulk; C_1206_3216Metric; MPN GRM31CR71E106KA12L
C5: 100n RADIO_DB_3V3 high-frequency; C_0603_1608Metric; MPN GRM188R71H104KA93D
H1, H2, H3, H4: M2 daughterboard support hole; MountingHole_2.2mm_M2
J1: FH12-30S 30-pin radio daughterboard FFC; Hirose_FH12-30S-0.5SH_1x30-1MP_P0.50mm_Horizontal; MPN FH12-30S-0.5SH(55)
U1: AP2112K-3.3 600mA daughterboard logic LDO; SOT-23-5; MPN AP2112K-3.3TRG1

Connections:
/GNSS_EXTINT: J1.29; also elsewhere on the board
/GNSS_PPS: J1.28; also elsewhere on the board
/GNSS_RESET_N: J1.27; also elsewhere on the board
/GNSS_UART_RX: J1.24; also elsewhere on the board
/GNSS_UART_TX: J1.25; also elsewhere on the board
/RADIO_CODEC_USB_DN: J1.9; also elsewhere on the board
/RADIO_CODEC_USB_DP: J1.8; also elsewhere on the board
/RADIO_CODEC_USB_VBUS: J1.5; also elsewhere on the board
/RADIO_DB_3V3: C3.1, C4.1, C5.1, U1.5 (VOUT); also elsewhere on the board
/RADIO_DB_5V: C1.1, C2.1, J1.2, J1.3, J1.6, U1.1 (VIN), U1.3 (EN); also elsewhere on the board
/RADIO_UHF_PD_N: J1.18; also elsewhere on the board
/RADIO_UHF_PTT_N: J1.16; also elsewhere on the board
/RADIO_UHF_RF_SEL_3V3: J1.23; also elsewhere on the board
/RADIO_UHF_SQL: J1.21; also elsewhere on the board
/RADIO_UHF_UART_RX: J1.14; also elsewhere on the board
/RADIO_UHF_UART_TX: J1.13; also elsewhere on the board
/RADIO_VHF_PD_N: J1.17; also elsewhere on the board
/RADIO_VHF_PTT_N: J1.15; also elsewhere on the board
/RADIO_VHF_RF_SEL_3V3: J1.22; also elsewhere on the board
/RADIO_VHF_SQL: J1.20; also elsewhere on the board
/RADIO_VHF_UART_RX: J1.12; also elsewhere on the board
/RADIO_VHF_UART_TX: J1.11; also elsewhere on the board
GND: C1.2, C2.2, C3.2, C4.2, C5.2, J1.1, J1.4, J1.7, J1.10, J1.19, J1.26, J1.30, J1.MP, U1.2 (GND); also elsewhere on the board

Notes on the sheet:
== Radio daughterboard connector and local logic supply ==
J1 pin 30 is the passive PRESENT_N strap: this board hard-connects it to GND.
== RADIO_DB_3V3 local logic regulator ==
RADIO_DB_5V feeds only the radio buck and local 3.3V regulator.
The PCM2902 radio codec is bus-powered from separately gated USB VBUS.
No daughterboard rail or signal is required for normal mainboard boot.
